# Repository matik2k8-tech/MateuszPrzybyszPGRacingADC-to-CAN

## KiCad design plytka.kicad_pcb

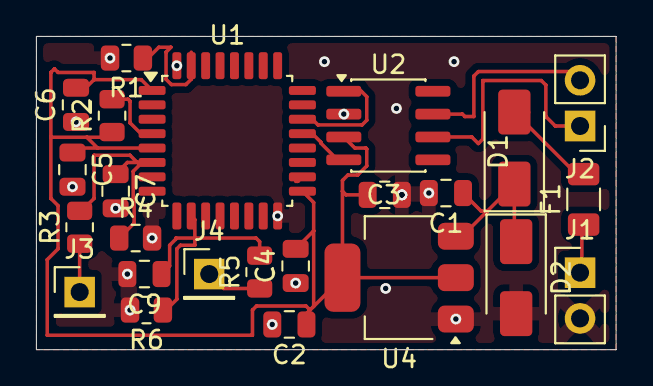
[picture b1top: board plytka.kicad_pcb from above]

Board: 2 copper layers, 32.2 x 17.4 mm, 24 parts (0 on the bottom side), 15 nets.

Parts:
C1, C2: 10µF; C_0805_2012Metric
C3: 100µF; C_0805_2012Metric
C4, C7, C9: 100nF; C_0805_2012Metric
C5, C6: C; C_0805_2012Metric
D1: SS34; D_SMA
D2: D_Schottky; D_SMA
F1: 1A; Fuse_1206_3216Metric
J1: 14.7V_IN; PinHeader_1x02_P2.54mm_Vertical
J2: Conn_01x02_Pin; PinHeader_1x02_P2.54mm_Vertical
J3, J4: Conn_01x01_Pin; PinHeader_1x01_P2.54mm_Vertical
R1: 10k; R_0805_2012Metric
R2: R; R_0805_2012Metric
R3, R5: 39K; R_0805_2012Metric
R4, R6: 9,1k; R_0805_2012Metric
U1: STM32F303K8Tx; LQFP-32_7x7mm_P0.8mm
U2: SN65HVD230; SOIC-8_3.9x4.9mm_P1.27mm
U4: AP1117-33; SOT-223-3_TabPin2

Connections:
/+14.7V: F1.1, J1.1
GND: C1.2, C2.2, C3.2, C4.1, C5.2, C6.1, C7.2, C9.2, D2.2 (A), J1.2, R1.2, R4.2, R6.2, U1.16 (VSS), U1.32 (VSS), U2.2 (GND), U4.1 (GND)
unnamed: D1.2 (A), F1.2
unnamed: C1.1, D1.1 (K), D2.1 (K), U4.3 (VI)
unnamed: J2.1, U2.6 (CANL)
unnamed: J2.2, U2.7 (CANH)
unnamed: J3.1 (Pin_1_1), R3.1
unnamed: J4.1 (Pin_1_1), R5.1
unnamed: R1.1, U1.31 (BOOT0)
unnamed: R2.2, U1.4 (NRST)
unnamed: C7.1, R3.2, R4.1, U1.6 (PA0)
unnamed: C9.1, R5.2, R6.1, U1.10 (PA4)
unnamed: U1.21 (PA11), U2.4 (R)
unnamed: U1.22 (PA12), U2.1 (D)
unnamed: C2.1, C3.1, C4.2, C5.1, C6.2, R2.1, U1.1 (VDD), U1.5 (VDDA), U1.17 (VDD), U2.3 (VCC), U4.2 (VO)
